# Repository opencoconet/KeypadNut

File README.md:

# KeypadNut
Keypad module for coconet

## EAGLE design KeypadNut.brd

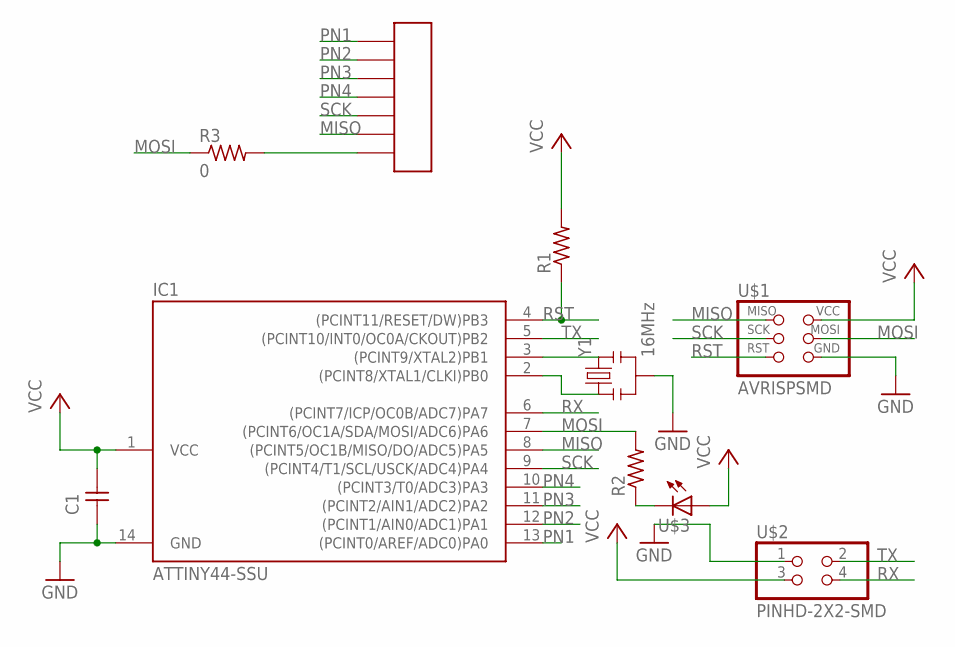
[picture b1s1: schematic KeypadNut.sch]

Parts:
C1: UNPOLARIZED_CAPACITOR1206; 1206
IC1: ATTINY44-SSU; SOIC14
R1, R2: RESISTOR1206; 1206
R3: 0; 1206
U$1: AVRISPSMD; 2X03SMD
U$2: PINHD-2X2-SMD; 2X02SMD
U$3: LED1206; 1206
U$4: 1X07-HEADER; 1X07-SMD
Y1: 16MHz; RESONATOR-SMD

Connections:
GND: C1.1, IC1.14 (GND), U$1.6 (GND), U$2.1, Y1.2
MISO: IC1.8 ((PCINT5/OC1B/MISO/DO/ADC5)PA5), U$1.1 (MISO), U$4.6
MOSI: IC1.7 ((PCINT6/OC1A/SDA/MOSI/ADC6)PA6), R2.2, R3.1, U$1.4 (MOSI)
unnamed: IC1.2 ((PCINT8/XTAL1/CLKI)PB0), Y1.1
unnamed: IC1.3 ((PCINT9/XTAL2)PB1), Y1.3
unnamed: R2.1, U$3.2 (C)
unnamed: R3.2, U$4.7
PN1: IC1.13 ((PCINT0/AREF/ADC0)PA0), U$4.1
PN2: IC1.12 ((PCINT1/AIN0/ADC1)PA1), U$4.2
PN3: IC1.11 ((PCINT2/AIN1/ADC2)PA2), U$4.3
PN4: IC1.10 ((PCINT3/T0/ADC3)PA3), U$4.4
RST: IC1.4 ((PCINT11/RESET/DW)PB3), R1.1, U$1.5 (RST)
RX: IC1.6 ((PCINT7/ICP/OC0B/ADC7)PA7), U$2.4
SCK: IC1.9 ((PCINT4/T1/SCL/USCK/ADC4)PA4), U$1.3 (SCK), U$4.5
TX: IC1.5 ((PCINT10/INT0/OC0A/CKOUT)PB2), U$2.2
VCC: C1.2, IC1.1 (VCC), R1.2, U$1.2 (VCC), U$2.3, U$3.1 (A)

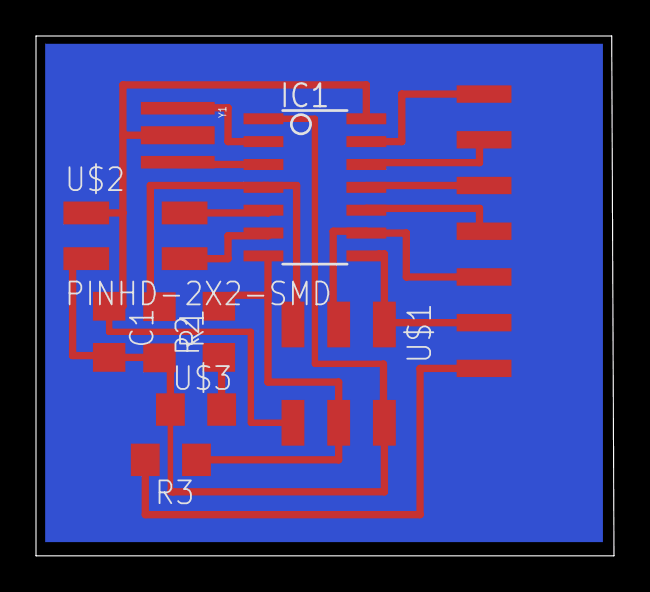
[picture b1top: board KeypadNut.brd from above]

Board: 2 copper layers, 32.1 x 28.9 mm, 10 parts (0 on the bottom side), 16 nets.

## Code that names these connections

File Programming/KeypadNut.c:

// ROW - PA0, PA1, PA2,PA3, PA4 and COL - PA5, PA6 and TX - PA7 and RX - PB2

#include <avr/io.h>
#include <util/delay.h>

#define output(directions,pin) (directions |= pin) // set port direction for output
#define input(directions,pin) (directions &= (~pin)) // set port direction for
#define set(port,pin) (port |= pin) // set port pin
#define clear(port,pin) (port &= (~pin)) // clear port pin
#define pin_test(pins,pin) (pins & pin) // test for port pin
#define bit_test(byte,bit) (byte & (1 << bit)) // test for bit set

// For Serial Communication
#define bit_delay_time 8.5 // bit delay for 115200 with overhead
#define bit_delay() _delay_us(bit_delay_time) // RS232 bit delay
#define half_bit_delay() _delay_us(bit_delay_time/2) // RS232 half bit delay
#define char_delay() _delay_ms(10) // char delay


/*******************************************

Function return keycode map

    [0x0B] [0x0A] [0x09]
    [0x08] [0x07] [0x06]
    [0x05] [0x04] [0x03]
    [0x02] [0x01] [0x00]

255 (hex 0xFF) if NO keypressed.
*******************************************/


uint8_t GetKeyPressed()
{
    uint8_t r,c;

    PORTA|= 0X0F;

    for(c=0;c<3;c++)
    {
        DDRA&=~(0X7F);

        DDRA|=(0X40>>c);

        for(r=0;r<4;r++)
        {
            if(!(PINA & (0X08>>r)))
            {
                return (r*3+c);
            }
         }
      }

      return 0XFF;//Indicate No key pressed
}


void put_char(volatile unsigned char *port, unsigned char pin, char txchar) {
   //
   // send character in txchar on port pin
   //    assumes line driver (inverts bits)
   //
   // start bit
   //
   clear(*port,pin);
   bit_delay();
   //
   // unrolled loop to write data bits
   //
   if bit_test(txchar,0)
      set(*port,pin);
   else
      clear(*port,pin);
   bit_delay();
   if bit_test(txchar,1)
      set(*port,pin);
   else
      clear(*port,pin);
   bit_delay();
   if bit_test(txchar,2)
      set(*port,pin);
   else
      clear(*port,pin);
   bit_delay();
   if bit_test(txchar,3)
      set(*port,pin);
   else
      clear(*port,pin);
   bit_delay();
   if bit_test(txchar,4)
      set(*port,pin);
   else
      clear(*port,pin);
   bit_delay();
   if bit_test(txchar,5)
      set(*port,pin);
   else
      clear(*port,pin);
   bit_delay();
   if bit_test(txchar,6)
      set(*port,pin);
   else
      clear(*port,pin);
   bit_delay();
   if bit_test(txchar,7)
      set(*port,pin);
   else
      clear(*port,pin);
   bit_delay();
   //
   // stop bit
   //
   set(*port,pin);
   bit_delay();
   //
   // char delay
   //
   bit_delay();

}


void flash() {
    output(DDRA,(1 << PA6));
    clear(PORTA, (1 << PA6));
    _delay_ms(50);
    set(PORTA, (1 << PA6));
    _delay_ms(50);
    clear(PORTA, (1 << PA6));
}


int main()
{

    static char chr = 'P';
    uint8_t key;

    // set clock divider to /1
    CLKPR = (1 << CLKPCE);
    CLKPR = (0 << CLKPS3) | (0 << CLKPS2) | (0 << CLKPS1) | (0 << CLKPS0);

    // Set PA7 as serial port output pin
    output(DDRA,(1 << PA7));

    while(1)
    {
    key=GetKeyPressed(); //Get the keycode of pressed key

        if (key == 0X0B)
        {
            put_char(&PORTA, (1 << PA7),0x31);
            flash();
        }
        else if (key == 0X0A)
        {
            put_char(&PORTA, (1 << PA7),0x32);
        }
        else if (key == 0X09)
        {
            put_char(&PORTA, (1 << PA7),0x33);
        }
        else if (key == 0X08)
        {
            put_char(&PORTA, (1 << PA7),0x34);
        }
        else if (key == 0X07)
        {
            put_char(&PORTA, (1 << PA7),0x35);
        }
        else if (key == 0X06)
        {
            put_char(&PORTA, (1 << PA7),0x36);
        }
        else if (key == 0X05)
        {
            put_char(&PORTA, (1 << PA7),0x37);
        }
        else if (key == 0X04)
        {
            put_char(&PORTA, (1 << PA7),0x38);
        }
        else if (key == 0X03)
        {
            put_char(&PORTA, (1 << PA7),0x39);
        }
        else if (key == 0X02)
        {
            put_char(&PORTA, (1 << PA7),0x2A);
        }
        else if (key == 0X01)
        {
            put_char(&PORTA, (1 << PA7),0x30);
        }
        else if (key == 0X00)
        {
            put_char(&PORTA, (1 << PA7),0x23);
        }
      }

}

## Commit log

2015-08-01 Changed template nut to add keypad
2015-08-03 Updated code for Keypad
